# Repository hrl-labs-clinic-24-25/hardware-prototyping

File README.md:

# hardware-prototyping
This repository contains the project files and intiial prototyping work which created the QUACK box. The published QUACK website may be found [here](https://hrl-labs-clinic-24-25.github.io/website/).

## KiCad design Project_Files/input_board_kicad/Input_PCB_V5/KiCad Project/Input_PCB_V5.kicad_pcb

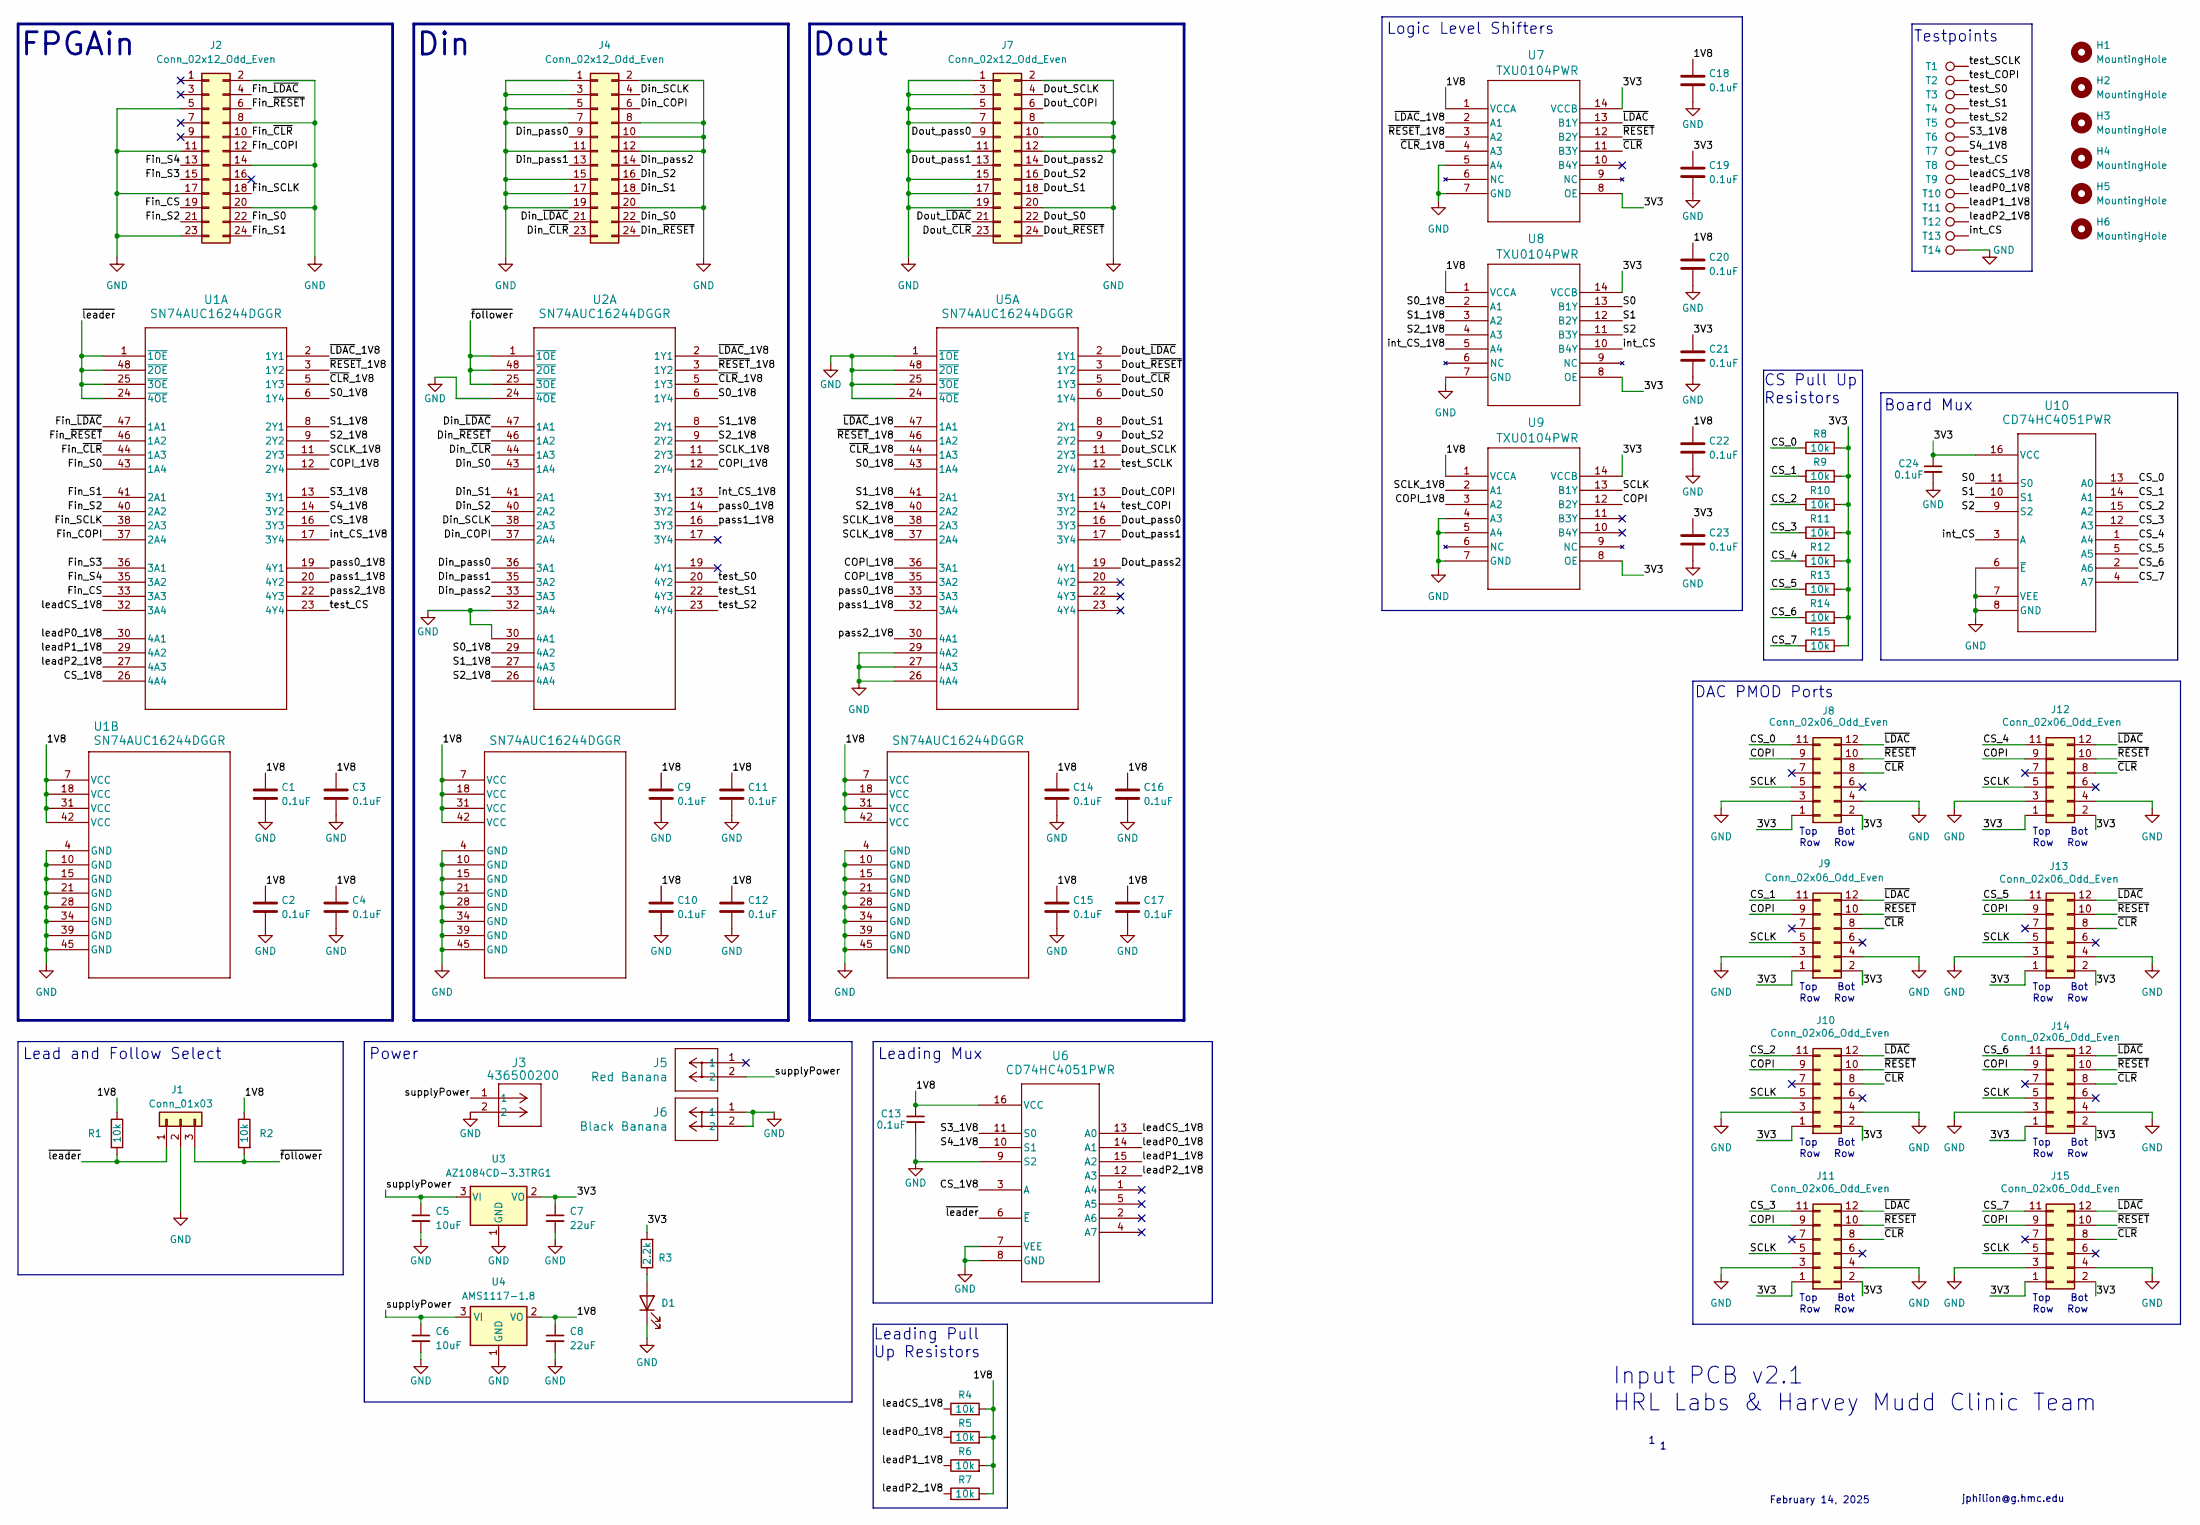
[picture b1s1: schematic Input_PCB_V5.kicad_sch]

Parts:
C1, C2, C3, C4, C9, C10, C11, C12, C13, C14, C15, C16, C17, C18, C19, C20, C21, C22, C23, C24: 0.1uF; C_0805_2012Metric
C5, C6: 10uF; C_0805_2012Metric
C7, C8: 22uF; C_0805_2012Metric
D1: HSMA-C170; LED_0805_2012Metric; JLCPCB Part # C7466711
H1, H2, H3, H4, H5, H6: MountingHole; MountingHole_3.2mm_M3
J1: Conn_01x03; PinHeader_1x03_P2.54mm_Vertical
J2, J4, J7: Conn_02x12_Odd_Even; IDC-Header_2x12_P2.54mm_Vertical; JLCPCB Part # C132440
J3: 436500200; CONN_SD-43650-001_02_MOL
J5: Red Banana; CONN-TH_24.243.2_Better_Silkscreen
J6: Black Banana; CONN-TH_24.243.2_Better_Silkscreen
J8, J9, J10, J11, J12, J13, J14, J15: Conn_02x06_Odd_Even; PinSocket_2x06_P2.54mm_Horizontal; JLCPCB Part # C2897426
R1, R2, R4, R5, R6, R7, R8, R9, R10, R11, R12, R13, R14, R15: 10k; R_0805_2012Metric
R3: 2.2k; R_0805_2012Metric
T1, T2, T3, T4, T5, T6, T7, T8, T9, T10, T11, T12, T13, T14: TestPoint; HARWIN_S1751-46R
U1, U2, U5: SN74AUC16244DGGR; DGG48
U3: AZ1084CD-3.3TRG1; TO-252-3_TabPin2; JLCPCB Part # C151391
U4: AMS1117-1.8; SOT-223-3_TabPin2; JLCPCB Part # C347220
U6, U10: CD74HC4051PWR; PW16
U7, U8, U9: TXU0104PWR; TSSOP_0104PWR_TEX

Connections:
/1V8: C1.1, C2.1, C3.1, C4.1, C8.1, C9.1, C10.1, C11.1, C12.1, C13.1, C14.1, C15.1, C16.1, C17.1, C18.1, C20.1, C22.1, R1.1, R2.1, R4.2, R5.2, R6.2, R7.2, U1.7 (VCC), U1.18 (VCC), U1.31 (VCC), U1.42 (VCC), U2.7 (VCC), U2.18 (VCC), U2.31 (VCC), U2.42 (VCC), U4.2 (VO), U5.7 (VCC), U5.18 (VCC), U5.31 (VCC), U5.42 (VCC), U6.16 (VCC), U7.1 (VCCA), U8.1 (VCCA), U9.1 (VCCA)
/3V3: C7.1, C19.1, C21.1, C23.1, C24.1, J8.1, J8.2, J9.1, J9.2, J10.1, J10.2, J11.1, J11.2, J12.1, J12.2, J13.1, J13.2, J14.1, J14.2, J15.1, J15.2, R3.2, R8.2, R9.2, R10.2, R11.2, R12.2, R13.2, R14.2, R15.2, U3.2 (VO), U7.8 (OE), U7.14 (VCCB), U8.8 (OE), U8.14 (VCCB), U9.8 (OE), U9.14 (VCCB), U10.16 (VCC)
/COPI: J8.9, J9.9, J10.9, J11.9, J12.9, J13.9, J14.9, J15.9, U9.12 (B2Y)
/COPI_1V8: U1.12 (2Y4), U2.12 (2Y4), U5.35 (3A2), U5.36 (3A1), U9.3 (A2)
/CS_0: J8.11, R8.1, U10.13 (A0)
/CS_1: J9.11, R9.1, U10.14 (A1)
/CS_1V8: U1.16 (3Y3), U1.26 (4A4), U6.3 (A)
/CS_2: J10.11, R10.1, U10.15 (A2)
/CS_3: J11.11, R11.1, U10.12 (A3)
/CS_4: J12.11, R12.1, U10.1 (A4)
/CS_5: J13.11, R13.1, U10.5 (A5)
/CS_6: J14.11, R14.1, U10.2 (A6)
/CS_7: J15.11, R15.1, U10.4 (A7)
/Din_COPI: J4.6, U2.37 (2A4)
/Din_S0: J4.22, U2.43 (1A4)
/Din_S1: J4.18, U2.41 (2A1)
/Din_S2: J4.16, U2.40 (2A2)
/Din_SCLK: J4.4, U2.38 (2A3)
/Din_pass0: J4.9, U2.36 (3A1)
/Din_pass1: J4.13, U2.35 (3A2)
/Din_pass2: J4.14, U2.33 (3A3)
/Din_~CLR: J4.23, U2.44 (1A3)
/Din_~LDAC: J4.21, U2.47 (1A1)
/Din_~RESET: J4.24, U2.46 (1A2)
/Dout_COPI: J7.6, U5.13 (3Y1)
/Dout_S0: J7.22, U5.6 (1Y4)
/Dout_S1: J7.18, U5.8 (2Y1)
/Dout_S2: J7.16, U5.9 (2Y2)
/Dout_SCLK: J7.4, U5.11 (2Y3)
/Dout_pass0: J7.9, U5.16 (3Y3)
/Dout_pass1: J7.13, U5.17 (3Y4)
/Dout_pass2: J7.14, U5.19 (4Y1)
/Dout_~CLR: J7.23, U5.5 (1Y3)
/Dout_~LDAC: J7.21, U5.2 (1Y1)
/Dout_~RESET: J7.24, U5.3 (1Y2)
/Fin_COPI: J2.12, U1.37 (2A4)
/Fin_CS: J2.19, U1.33 (3A3)
/Fin_S0: J2.22, U1.43 (1A4)
/Fin_S1: J2.24, U1.41 (2A1)
/Fin_S2: J2.21, U1.40 (2A2)
/Fin_S3: J2.15, U1.36 (3A1)
/Fin_S4: J2.13, U1.35 (3A2)
/Fin_SCLK: J2.18, U1.38 (2A3)
/Fin_~CLR: J2.10, U1.44 (1A3)
/Fin_~LDAC: J2.4, U1.47 (1A1)
/Fin_~RESET: J2.6, U1.46 (1A2)
/S0: U8.13 (B1Y), U10.11 (S0)
/S0_1V8: U1.6 (1Y4), U2.6 (1Y4), U2.29 (4A2), U5.43 (1A4), U8.2 (A1)
/S1: U8.12 (B2Y), U10.10 (S1)
/S1_1V8: U1.8 (2Y1), U2.8 (2Y1), U2.27 (4A3), U5.41 (2A1), U8.3 (A2)
/S2: U8.11 (B3Y), U10.9 (S2)
/S2_1V8: U1.9 (2Y2), U2.9 (2Y2), U2.26 (4A4), U5.40 (2A2), U8.4 (A3)
/S3_1V8: T6.1, U1.13 (3Y1), U6.11 (S0)
/S4_1V8: T7.1, U1.14 (3Y2), U6.10 (S1)
/SCLK: J8.5, J9.5, J10.5, J11.5, J12.5, J13.5, J14.5, J15.5, U9.13 (B1Y)
/SCLK_1V8: U1.11 (2Y3), U2.11 (2Y3), U5.37 (2A4), U5.38 (2A3), U9.2 (A1)
/int_CS: T13.1, U8.10 (B4Y), U10.3 (A)
/int_CS_1V8: U1.17 (3Y4), U2.13 (3Y1), U8.5 (A4)
/leadCS_1V8: R4.1, T9.1, U1.32 (3A4), U6.13 (A0)
/leadP0_1V8: R5.1, T10.1, U1.30 (4A1), U6.14 (A1)
/leadP1_1V8: R6.1, T11.1, U1.29 (4A2), U6.15 (A2)
/leadP2_1V8: R7.1, T12.1, U1.27 (4A3), U6.12 (A3)
/pass0_1V8: U1.19 (4Y1), U2.14 (3Y2), U5.33 (3A3)
/pass1_1V8: U1.20 (4Y2), U2.16 (3Y3), U5.32 (3A4)
/pass2_1V8: U1.22 (4Y3), U5.30 (4A1)
/supplyPower: C5.1, C6.1, J3.1, J5.2, U3.3 (VI), U4.3 (VI)
/test_COPI: T2.1, U5.14 (3Y2)
/test_CS: T8.1, U1.23 (4Y4)
/test_S0: T3.1, U2.20 (4Y2)
/test_S1: T4.1, U2.22 (4Y3)
/test_S2: T5.1, U2.23 (4Y4)
/test_SCLK: T1.1, U5.12 (2Y4)
/~CLR: J8.8, J9.8, J10.8, J11.8, J12.8, J13.8, J14.8, J15.8, U7.11 (B3Y)
/~CLR_1V8: U1.5 (1Y3), U2.5 (1Y3), U5.44 (1A3), U7.4 (A3)
/~LDAC: J8.12, J9.12, J10.12, J11.12, J12.12, J13.12, J14.12, J15.12, U7.13 (B1Y)
/~LDAC_1V8: U1.2 (1Y1), U2.2 (1Y1), U5.47 (1A1), U7.2 (A1)
/~RESET: J8.10, J9.10, J10.10, J11.10, J12.10, J13.10, J14.10, J15.10, U7.12 (B2Y)
/~RESET_1V8: U1.3 (1Y2), U2.3 (1Y2), U5.46 (1A2), U7.3 (A2)
/~follower: J1.3, R2.2, U2.1 (~1OE), U2.25 (~3OE), U2.48 (~2OE)
/~leader: J1.1, R1.2, U1.1 (~1OE), U1.24 (~4OE), U1.25 (~3OE), U1.48 (~2OE), U6.6 (~E)
GND: C1.2, C2.2, C3.2, C4.2, C5.2, C6.2, C7.2, C8.2, C9.2, C10.2, C11.2, C12.2, C13.2, C14.2, C15.2, C16.2, C17.2, C18.2, C19.2, C20.2, C21.2, C22.2, C23.2, C24.2, D1.1 (K), J1.2, J2.2, J2.5, J2.8, J2.11, J2.14, J2.17, J2.20, J2.23, J3.2, J4.1, J4.2, J4.3, J4.5, J4.7, J4.8, J4.10, J4.11, J4.12, J4.15, J4.17, J4.19, J4.20, J6.1, J6.2, J7.1, J7.2, J7.3, J7.5, J7.7, J7.8, J7.10, J7.11, J7.12, J7.15, J7.17, J7.19, J7.20, J8.3, J8.4, J9.3, J9.4, J10.3, J10.4, J11.3, J11.4, J12.3, J12.4, J13.3, J13.4, J14.3, J14.4, J15.3, J15.4, T14.1, U1.4 (GND), U1.10 (GND), U1.15 (GND), U1.21 (GND), U1.28 (GND), U1.34 (GND), U1.39 (GND), U1.45 (GND), U2.4 (GND), U2.10 (GND), U2.15 (GND), U2.21 (GND), U2.24 (~4OE), U2.28 (GND), U2.30 (4A1), U2.32 (3A4), U2.34 (GND), U2.39 (GND), U2.45 (GND), U3.1 (GND), U4.1 (GND), U5.1 (~1OE), U5.4 (GND), U5.10 (GND), U5.15 (GND), U5.21 (GND), U5.24 (~4OE), U5.25 (~3OE), U5.26 (4A4), U5.27 (4A3), U5.28 (GND), U5.29 (4A2), U5.34 (GND), U5.39 (GND), U5.45 (GND), U5.48 (~2OE), U6.7 (VEE), U6.8 (GND), U6.9 (S2), U7.5 (A4), U7.7 (GND), U8.7 (GND), U9.4 (A3), U9.5 (A4), U9.7 (GND), U10.6 (~E), U10.7 (VEE), U10.8 (GND)
unnamed: D1.2 (A), R3.1

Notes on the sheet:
Bot Row
Leading Pull Up Resistors
DAC PMOD Ports
Top Row
Testpoints
Board Mux
Leading Mux
February 14, 2025
Din
Dout
Input PCB v2.1 HRL Labs & Harvey Mudd Clinic Team
jphilion@g.hmc.edu
FPGAin
CS Pull Up Resistors
Lead and Follow Select
Logic Level Shifters
Power

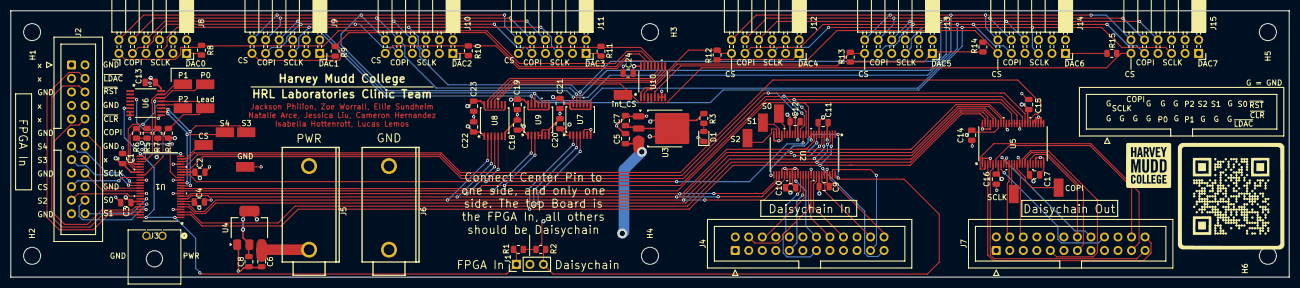
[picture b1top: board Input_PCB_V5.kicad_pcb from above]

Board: 4 copper layers, 240.0 x 50.0 mm, 85 parts (0 on the bottom side), 82 nets.

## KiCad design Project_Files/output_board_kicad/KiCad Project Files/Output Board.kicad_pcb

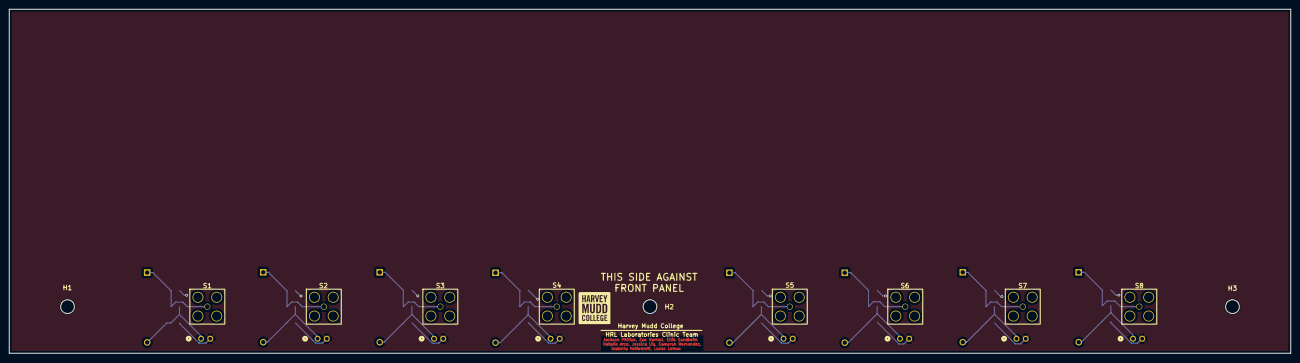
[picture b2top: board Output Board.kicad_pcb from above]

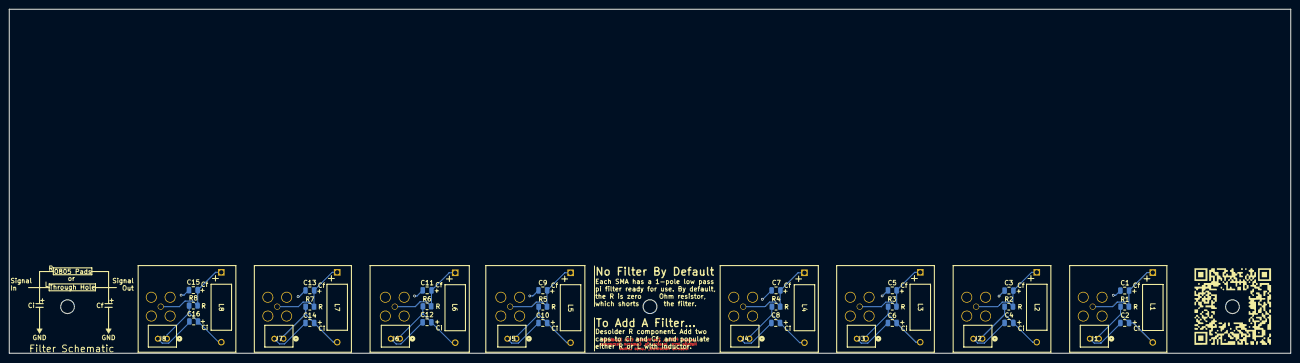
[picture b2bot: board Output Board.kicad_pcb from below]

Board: 2 copper layers, 279.4 x 75.0 mm, 52 parts (40 on the bottom side), 17 nets.

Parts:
  : LOGO; Footprint_HMC
C1, C2, C3, C4, C5, C6, C7, C8, C9, C10, C11, C12, C13, C14, C15, C16: C; C_0805_2012Metric
H1, H2, H3: MountingHole; MountingHole_3mm
J1, J2, J3, J4, J5, J6, J7, J8: B2B-PH-K-SLFSN; CONN_B2B-PH-K-SLFSN_JST
L1, L2, L3, L4, L5, L6, L7, L8: L; IND_1537R_API
R1, R2, R3, R4, R5, R6, R7, R8: 0; R_0805_2012Metric
S1, S2, S3, S4, S5, S6, S7, S8: SMA_CONNECTOR; HJ-SMA993

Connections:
GND: C1.2, C2.2, C3.2, C4.2, C5.2, C6.2, C7.2, C8.2, C9.2, C10.2, C11.2, C12.2, C13.2, C14.2, C15.2, C16.2, J1.2, J2.2, J3.2, J4.2, J5.2, J6.2, J7.2, J8.2
unnamed: C1.1, L1.1, R1.1, S1.1
unnamed: C2.1, J1.1, L1.2, R1.2
unnamed: C3.1, L2.1, R2.1, S2.1
unnamed: C4.1, J2.1, L2.2, R2.2
unnamed: C5.1, L3.1, R3.1, S3.1
unnamed: C6.1, J3.1, L3.2, R3.2
unnamed: C7.1, L4.1, R4.1, S4.1
unnamed: C8.1, J4.1, L4.2, R4.2
unnamed: C9.1, L5.1, R5.1, S5.1
unnamed: C10.1, J5.1, L5.2, R5.2
unnamed: C11.1, L6.1, R6.1, S6.1
unnamed: C12.1, J6.1, L6.2, R6.2
unnamed: C13.1, L7.1, R7.1, S7.1
unnamed: C14.1, J7.1, L7.2, R7.2
unnamed: C15.1, L8.1, R8.1, S8.1
unnamed: C16.1, J8.1, L8.2, R8.2

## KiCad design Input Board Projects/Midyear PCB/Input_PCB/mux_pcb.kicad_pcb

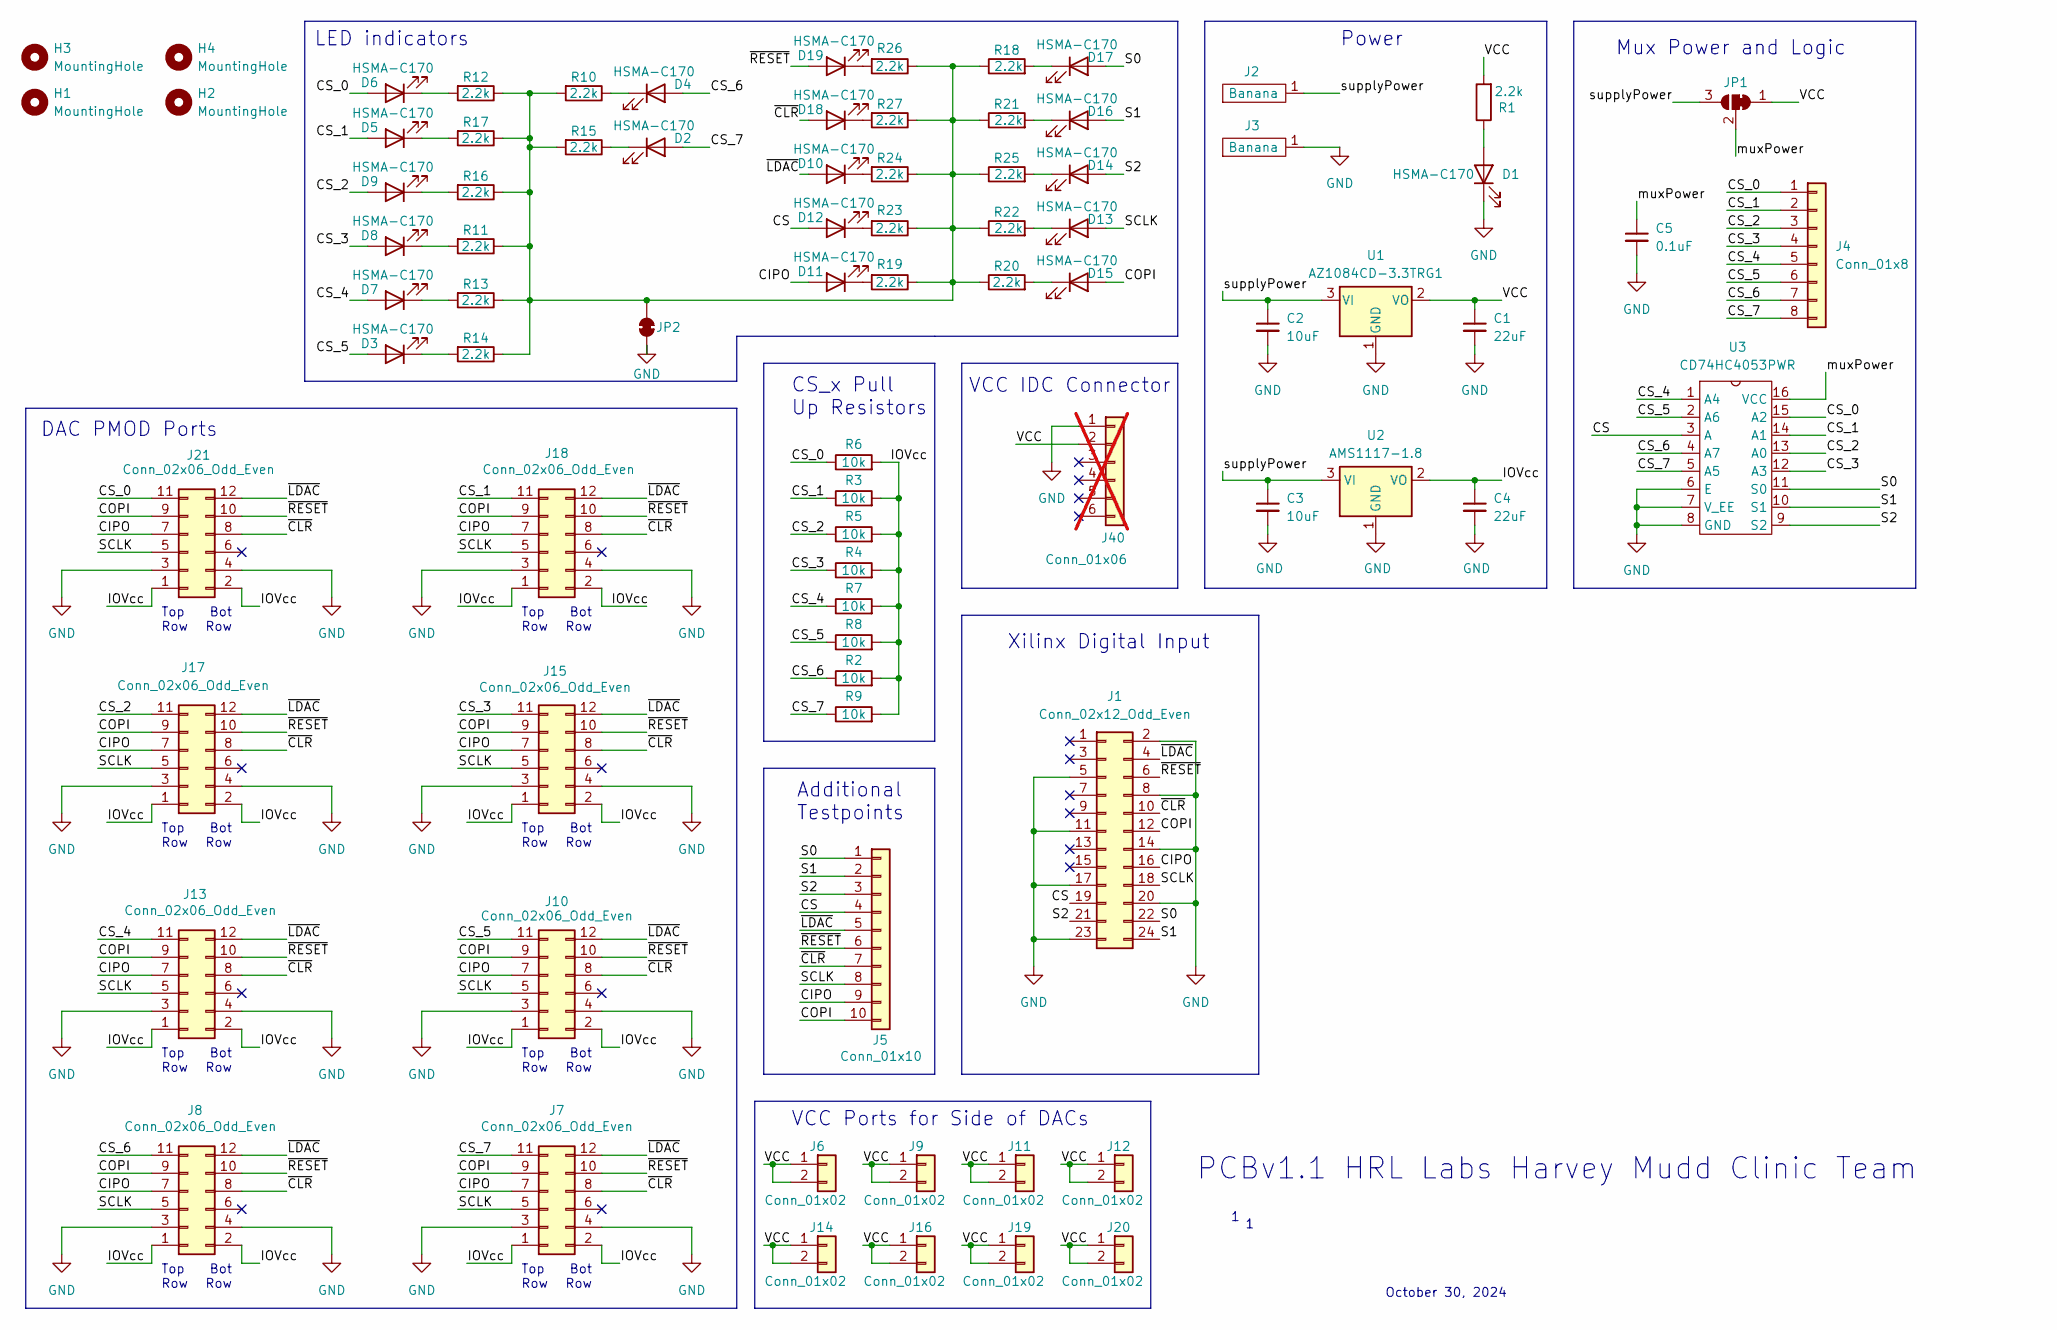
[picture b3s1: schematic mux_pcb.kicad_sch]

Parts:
C1, C4: 22uF; C_0805_2012Metric
C2, C3: 10uF; C_0805_2012Metric
C5: 0.1uF; C_0805_2012Metric
D1, D2, D3, D4, D5, D6, D7, D8, D9, D10, D11, D12, D13, D14, D15, D16, D17, D18, D19: HSMA-C170; LED_0805_2012Metric; JLCPCB Part # C7466711
H1, H2, H3, H4: MountingHole; MountingHole_3.2mm_M3
J1: Conn_02x12_Odd_Even; IDC-Header_2x12_P2.54mm_Vertical; JLCPCB Part # C132440
J2: Banana; MountingHole_6.4mm_M6_DIN965_Pad; JLCPCB Part # C106273
J3: Banana; MountingHole_6.4mm_M6_DIN965_Pad; JLCPCB Part # C106272
J4: Conn_01x8; PinHeader_1x08_P2.54mm_Vertical; JLCPCB Part # C2829996
J5: Conn_01x10; PinHeader_1x10_P2.54mm_Vertical; JLCPCB Part # C5156617
J6, J9, J11, J12, J14, J16, J19, J20: Conn_01x02; PinSocket_1x02_P2.54mm_Vertical; JLCPCB Part # C49661
J7, J8, J10, J13, J15, J17, J18, J21: Conn_02x06_Odd_Even; PinSocket_2x06_P2.54mm_Horizontal; JLCPCB Part # C2897426
J40: Conn_01x06; not fitted
JP1: SolderJumper_3_Bridged12; SolderJumper-3_P1.3mm_Bridged12_RoundedPad1.0x1.5mm
JP2: SolderJumper_2_Bridged; SolderJumper-2_P1.3mm_Bridged_RoundedPad1.0x1.5mm
R1, R10, R11, R12, R13, R14, R15, R16, R17, R18, R19, R20, R21, R22, R23, R24, R25, R26, R27: 2.2k; R_0805_2012Metric
R2, R3, R4, R5, R6, R7, R8, R9: 10k; R_0805_2012Metric
U1: AZ1084CD-3.3TRG1; TO-252-3_TabPin2; JLCPCB Part # C151391
U2: AMS1117-1.8; SOT-223-3_TabPin2; JLCPCB Part # C347220
U3: CD74HC4053PWR; TSSOP-16_4.4x5mm_P0.65mm; JLCPCB Part # C6546

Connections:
/CIPO: D11.2 (A), J1.16, J5.9, J7.7, J8.7, J10.7, J13.7, J15.7, J17.7, J18.7, J21.7
/COPI: D15.2 (A), J1.12, J5.10, J7.9, J8.9, J10.9, J13.9, J15.9, J17.9, J18.9, J21.9
/CS: D12.2 (A), J1.19, J5.4, U3.3 (A)
/CS_0: D6.2 (A), J4.1, J21.11, R6.1, U3.15 (A2)
/CS_1: D5.2 (A), J4.2, J18.11, R3.1, U3.14 (A1)
/CS_2: D9.2 (A), J4.3, J17.11, R5.1, U3.13 (A0)
/CS_3: D8.2 (A), J4.4, J15.11, R4.1, U3.12 (A3)
/CS_4: D7.2 (A), J4.5, J13.11, R7.1, U3.1 (A4)
/CS_5: D3.2 (A), J4.6, J10.11, R8.1, U3.2 (A6)
/CS_6: D4.2 (A), J4.7, J8.11, R2.1, U3.4 (A7)
/CS_7: D2.2 (A), J4.8, J7.11, R9.1, U3.5 (A5)
/IOVcc: C4.1, J7.1, J7.2, J8.1, J8.2, J10.1, J10.2, J13.1, J13.2, J15.1, J15.2, J17.1, J17.2, J18.1, J18.2, J21.1, J21.2, R2.2, R3.2, R4.2, R5.2, R6.2, R7.2, R8.2, R9.2, U2.2 (VO)
/S0: D17.2 (A), J1.22, J5.1, U3.11 (S0)
/S1: D16.2 (A), J1.24, J5.2, U3.10 (S1)
/S2: D14.2 (A), J1.21, J5.3, U3.9 (S2)
/SCLK: D13.2 (A), J1.18, J5.8, J7.5, J8.5, J10.5, J13.5, J15.5, J17.5, J18.5, J21.5
/VCC: C1.1, J6.1, J6.2, J9.1, J9.2, J11.1, J11.2, J12.1, J12.2, J14.1, J14.2, J16.1, J16.2, J19.1, J19.2, J20.1, J20.2, J40.2, JP1.1 (A), R1.2, U1.2 (VO)
/muxPower: C5.1, JP1.2 (C), U3.16 (VCC)
/supplyPower: C2.1, C3.1, J2.1, JP1.3 (B), U1.3 (VI), U2.3 (VI)
/~CLR: D18.2 (A), J1.10, J5.7, J7.8, J8.8, J10.8, J13.8, J15.8, J17.8, J18.8, J21.8
/~LDAC: D10.2 (A), J1.4, J5.5, J7.12, J8.12, J10.12, J13.12, J15.12, J17.12, J18.12, J21.12
/~RESET: D19.2 (A), J1.6, J5.6, J7.10, J8.10, J10.10, J13.10, J15.10, J17.10, J18.10, J21.10
GND: C1.2, C2.2, C3.2, C4.2, C5.2, D1.1 (K), J1.2, J1.5, J1.8, J1.11, J1.14, J1.17, J1.20, J1.23, J3.1, J7.3, J7.4, J8.3, J8.4, J10.3, J10.4, J13.3, J13.4, J15.3, J15.4, J17.3, J17.4, J18.3, J18.4, J21.3, J21.4, J40.1, JP2.1 (A), U1.1 (GND), U2.1 (GND), U3.6 (E), U3.7 (V_EE), U3.8 (GND)
unnamed: D1.2 (A), R1.1
unnamed: D2.1 (K), R15.1
unnamed: D3.1 (K), R14.2
unnamed: D4.1 (K), R10.1
unnamed: D5.1 (K), R17.2
unnamed: D6.1 (K), R12.2
unnamed: D7.1 (K), R13.2
unnamed: D8.1 (K), R11.2
unnamed: D9.1 (K), R16.2
unnamed: D10.1 (K), R24.2
unnamed: D11.1 (K), R19.2
unnamed: D12.1 (K), R23.2
unnamed: D13.1 (K), R22.2
unnamed: D14.1 (K), R25.2
unnamed: D15.1 (K), R20.2
unnamed: D16.1 (K), R21.2
unnamed: D17.1 (K), R18.2
unnamed: D18.1 (K), R27.2
unnamed: D19.1 (K), R26.2
unnamed: JP2.2 (B), R10.2, R11.1, R12.1, R13.1, R14.1, R15.2, R16.1, R17.1, R18.1, R19.1, R20.1, R21.1, R22.1, R23.1, R24.1, R25.1, R26.1, R27.1

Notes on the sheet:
CS_x Pull Up Resistors
Power
PCBv1.1 HRL Labs Harvey Mudd Clinic Team
DAC PMOD Ports
Bot Row
LED indicators
Top Row
VCC Ports for Side of DACs
Xilinx Digital Input
Additional Testpoints
VCC IDC Connector
Mux Power and Logic
October 30, 2024

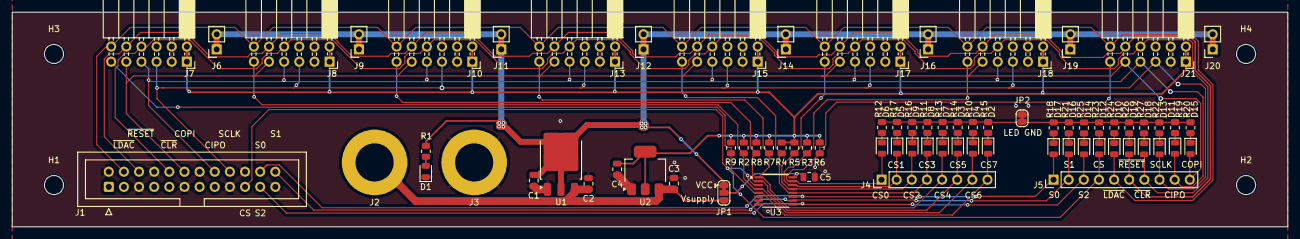
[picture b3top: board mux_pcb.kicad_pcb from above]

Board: 2 copper layers, 214.0 x 36.0 mm, 81 parts (0 on the bottom side), 43 nets.

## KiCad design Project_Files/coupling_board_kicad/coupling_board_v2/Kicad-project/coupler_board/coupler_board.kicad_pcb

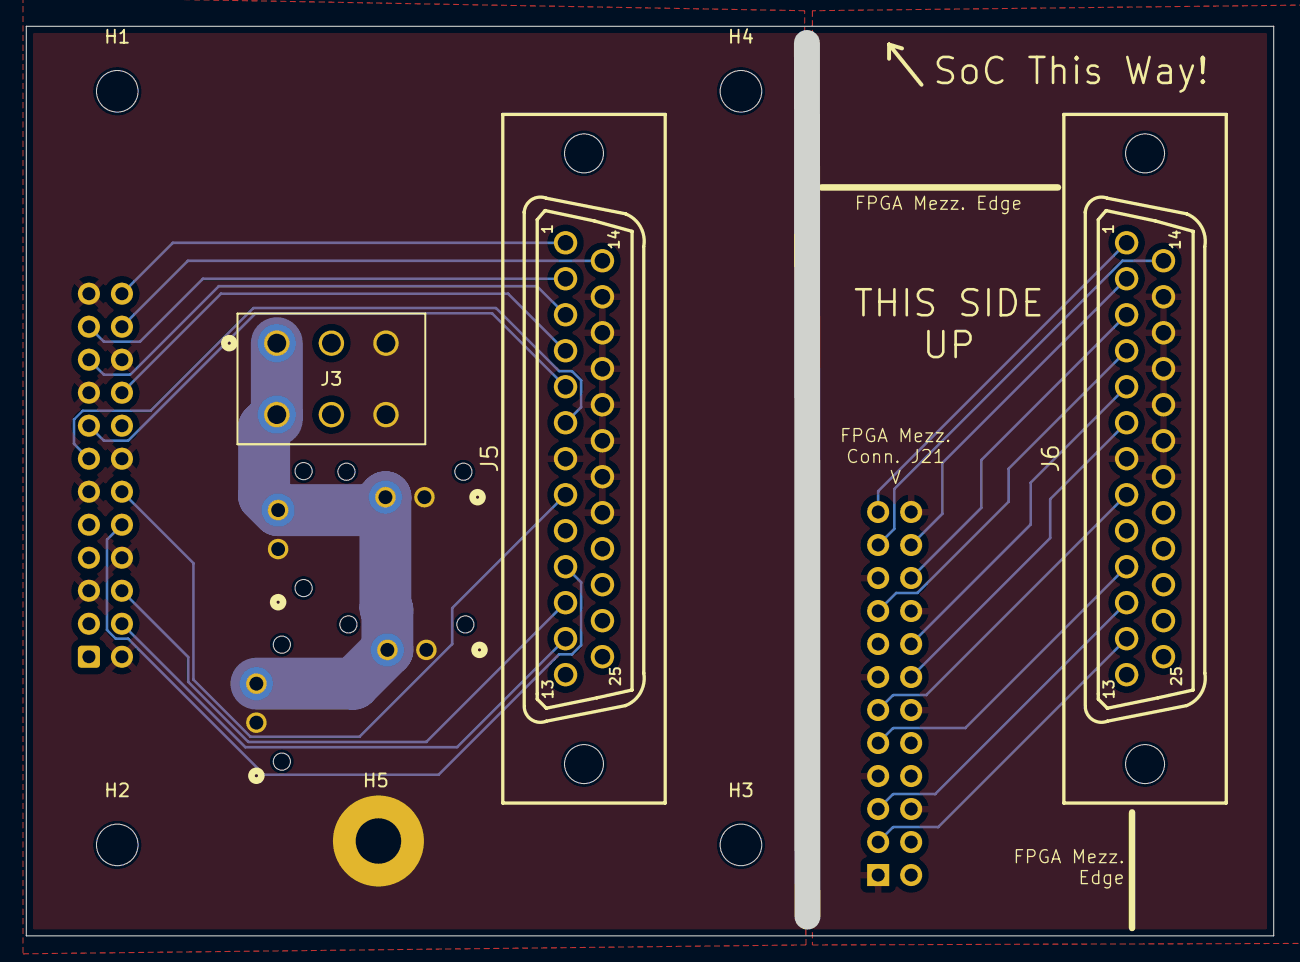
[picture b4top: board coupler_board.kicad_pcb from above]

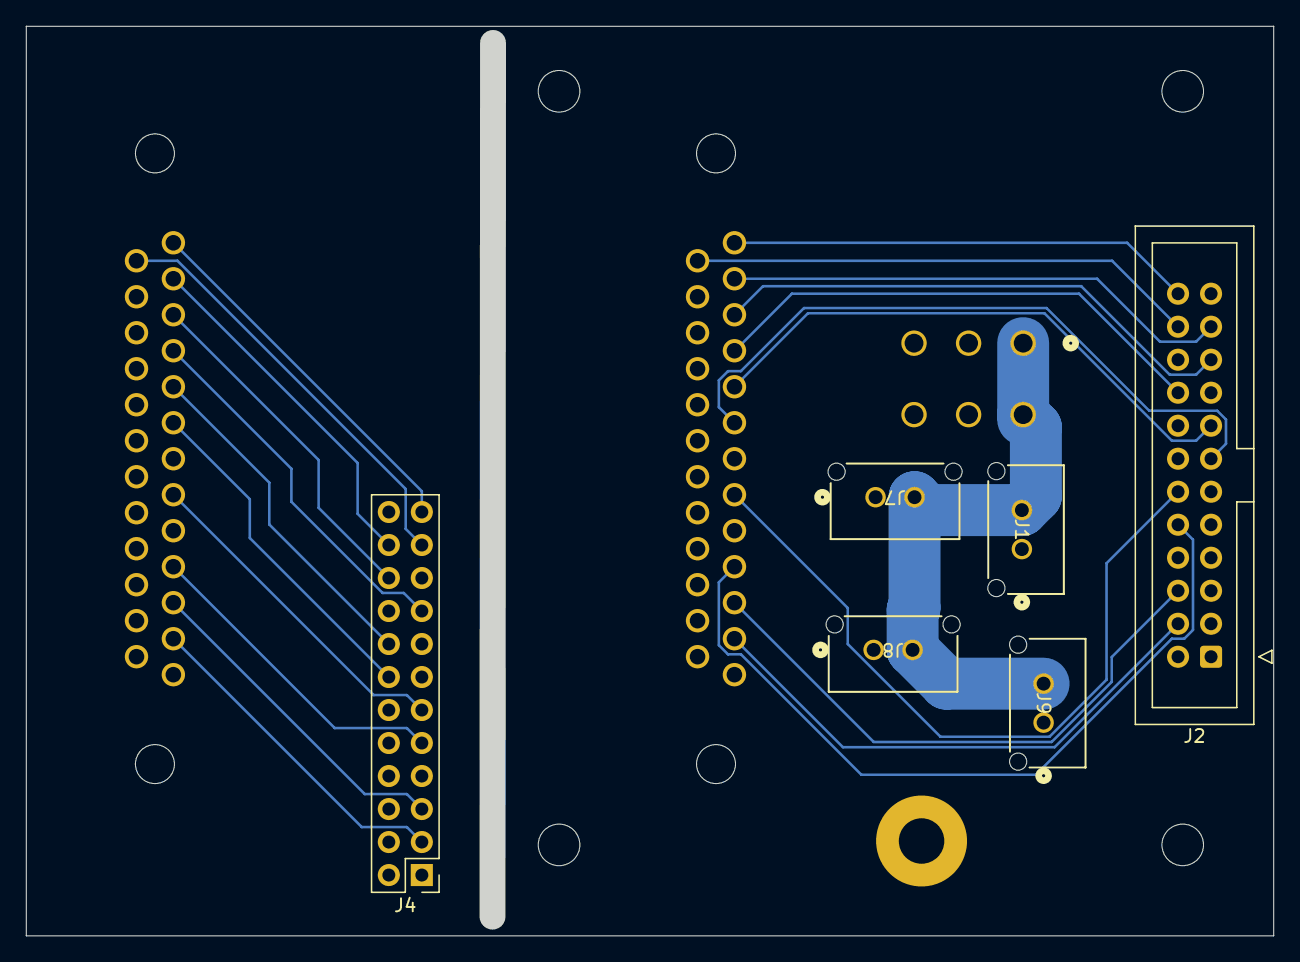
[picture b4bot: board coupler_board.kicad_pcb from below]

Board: 2 copper layers, 96.0 x 70.0 mm, 14 parts (6 on the bottom side), 25 nets.

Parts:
H1, H2, H3, H4: MountingHole; MountingHole_3.2mm_M3
H5: MountingHole_Pad; MountingHole_3.5mm_Pad
J1, J7, J8, J9: Molex Microfit; CONN_SD-43650-006_02_MOL
J2: Conn_02x12_Odd_Even; IDC-Header_2x12_P2.54mm_Vertical
J3: Molex6; CONN_0039281063_5566-06A_MOL
J4: Conn_02x12_Odd_Even; PinHeader_2x12_P2.54mm_Vertical
J5, J6: DB25_Socket; DSUB-TH_DS1034-25FUNSI44

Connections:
/Fin_COPI: J2.12, J5.8
/Fin_CS: J2.19, J5.3
/Fin_S0: J2.22, J5.14
/Fin_S1: J2.24, J5.1
/Fin_S2: J2.21, J5.2
/Fin_S3: J2.15, J5.5
/Fin_S4: J2.13, J5.6
/Fin_SCLK: J2.18, J5.4
/Fin_~CLR: J2.10, J5.10
/Fin_~LDAC: J2.4, J5.12
/Fin_~RESET: J2.6, J5.11
/supplyP: J1.2, J3.1, J3.2, J7.2, J8.2, J9.2
/vcut_COPI: J4.11, J6.8
/vcut_CS: J4.20, J6.3
/vcut_S0: J4.21, J6.14
/vcut_S1: J4.23, J6.1
/vcut_S2: J4.22, J6.2
/vcut_S3: J4.16, J6.5
/vcut_S4: J4.14, J6.6
/vcut_SCLK: J4.17, J6.4
/vcut_~CLR: J4.9, J6.10
/vcut_~LDAC: J4.3, J6.12
/vcut_~RESET: J4.5, J6.11
GND: H5.1, J1.1, J2.2, J2.5, J2.8, J2.11, J2.14, J2.17, J2.20, J2.23, J3.5, J3.6, J5.7, J5.15, J5.16, J5.17, J5.18, J5.19, J5.20, J5.21, J7.1, J8.1, J9.1
GND_Vcut: J4.1, J4.6, J4.7, J4.12, J4.13, J4.18, J4.19, J4.24, J6.7, J6.15, J6.16, J6.17, J6.18, J6.19, J6.20

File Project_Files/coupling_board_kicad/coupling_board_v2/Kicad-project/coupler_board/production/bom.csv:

Designator,Footprint,Quantity,Value,LCSC Part #
H5,MountingHole_3.5mm_Pad,1,MountingHole_Pad,
"J1, J7, J8, J9",CONN_SD-43650-006_02_MOL,4,Molex Microfit,
J2,IDC-Header_2x12_P2.54mm_Vertical,1,Conn_02x12_Odd_Even,C132440
J3,CONN_0039281063_5566-06A_MOL,1,Molex6,
J4,PinHeader_2x12_P2.54mm_Vertical,1,Conn_02x12_Odd_Even,C132440
"J5, J6",DSUB-TH_DS1034-25FUNSI44,2,DB25_Socket,

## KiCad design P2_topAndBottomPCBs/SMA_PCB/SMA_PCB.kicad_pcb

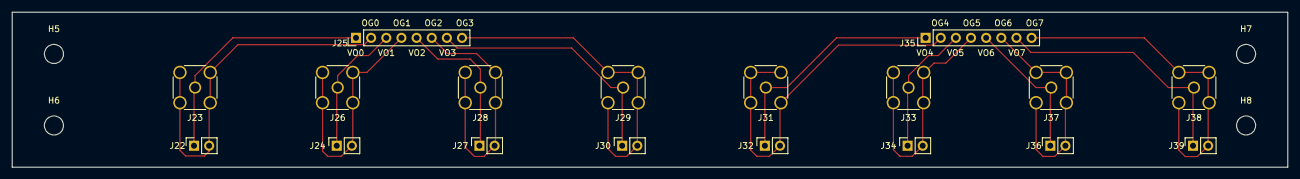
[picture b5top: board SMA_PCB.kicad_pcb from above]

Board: 2 copper layers, 214.0 x 26.0 mm, 22 parts (0 on the bottom side), 16 nets.

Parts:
H5, H6, H7, H8: MountingHole; MountingHole_3.2mm_M3
J22, J24, J27, J30, J32, J34, J36, J39: Conn_01x02; PinSocket_1x02_P2.54mm_Vertical
J23, J26, J28, J29, J31, J33, J37, J38: SMA_Amphenol_132134-16_Vertical
J25, J35: Conn_01x8; PinHeader_1x08_P2.54mm_Vertical

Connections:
/OGND_0: J22.2, J23.2, J25.2
/OGND_1: J24.2, J25.4, J26.2
/OGND_2: J25.6, J27.2, J28.2
/OGND_3: J25.8, J29.2, J30.2
/OGND_4: J31.2, J32.2, J35.2
/OGND_5: J33.2, J34.2, J35.4
/OGND_6: J35.6, J36.2, J37.2
/OGND_7: J35.8, J38.2, J39.2
/Vout_0: J22.1, J23.1, J25.1
/Vout_1: J24.1, J25.3, J26.1
/Vout_2: J25.5, J27.1, J28.1
/Vout_3: J25.7, J29.1, J30.1
/Vout_4: J31.1, J32.1, J35.1
/Vout_5: J33.1, J34.1, J35.3
/Vout_6: J35.5, J36.1, J37.1
/Vout_7: J35.7, J38.1, J39.1

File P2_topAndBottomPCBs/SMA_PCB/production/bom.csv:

Designator,Footprint,Quantity,Value,LCSC Part #
"J22, J24, J27, J30, J32, J34, J36, J39",PinSocket_1x02_P2.54mm_Vertical,8,Conn_01x02,C49661
"J23, J26, J28, J29, J31, J33, J37, J38",SMA_Amphenol_132134-16_Vertical,8,~,C496549
"J25, J35",PinHeader_1x08_P2.54mm_Vertical,2,Conn_01x8,C2829996

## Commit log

2024-10-01 Jackson's added Sep.30 work
2024-10-01 Add CN0531 Schematic
2024-10-02 Add work Oct.1, basically shuffling code to get CN to work
2024-10-06 Got SPI working!
    Current binary word should output +5V to the DAC. Also sets the Teensy clock to 4 MHz
2024-10-06 Add CD74 to Schematic
2024-10-09 Got 2 CS working
    In a "Prototype 2" folder.
    Also modified SPIspew in Prototype1.
2024-10-10 Tried setting up SDO - still buggy
    Added Prototype 3 folder with new sketch
2024-10-19 Jackson's P1 Mux Changes
2024-10-19 Fix SPIspew changes
2024-10-19 Organization
2024-10-20 Almost have daisy-chaining working
    For some reason the SDO on DAC 1 was outputting a signal, but SDI on DAC 2 had no signal? I think?
2024-10-22 2mux Working
2024-10-23 Got daisychain working!
    It's still buggy/working inconsistently, but it works!
2024-10-30 Jackson Schematic Work
2024-11-05 Schematic Draft 1
2024-11-06 Final Draft Schematic
2024-11-06 Update 1x2 Headers on Vcc
2024-11-06 First Draft of PCB
    Haven't routed traces in case of major feedback from Prof. Brake tomorrow
2024-11-07 a few edits to PCB P1
    based on design review. still need to route traces
2024-11-07 minor tweaks to PCB
2024-11-09 PCB finished!
    Haven't thoroughly looked it over yet
2024-11-09 nvm it's not done
    fixed most of the problem
2024-11-09 PCB Finalized & Ordered!
    Had to manually fix a number of things (e.g. component rotation) when I ordered it on JLCPCB. I didn't add the settings that let you rotate the part automatically into the right position.
2024-11-11 Separated PCB into two PCBS
    Ordering as one PCB w/ V-cut was more expensive. Also fixed placement for JLCPCB orders and narrowed the mux board since it no longer needs to be 70mm wide
2024-11-13 KiCAD stuff
    tbh i'm not sure what I did here
2025-04-26 Reorganizing
2025-04-26 push coupling board, support panel, front panel
2025-04-27 Output Board Project Files
2025-05-12 push coupling board revision
2025-05-15 File Reorganization
2025-05-15 Input Board Updates
2025-06-05 Removed question-mark, made valid filename
2025-06-05 Fixed some footprint filenames that were too long
2025-06-05 Fixed filename that was too long
